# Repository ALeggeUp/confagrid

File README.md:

# Confagrid

What is it?
-----------

Text grid generator tool

Contributors
------------

* [Stephen Legge](https://github.com/slegge)

How to use
----------

* Run `./mvnw package` or `mvnw.cmd package` depending on your platform to compile
* Start the server with `java -jar application/confagrid-webapp/target/confagrid-webapp-0.9.0-SNAPSHOT.jar`
* Open your browser and go to 'http://localhost:8080/'

License
-------

MIT License

Copyright (c) 2017-2018 [ A Legge Up ]

Permission is hereby granted, free of charge, to any person obtaining a copy
of this software and associated documentation files (the "Software"), to deal
in the Software without restriction, including without limitation the rights
to use, copy, modify, merge, publish, distribute, sublicense, and/or sell
copies of the Software, and to permit persons to whom the Software is
furnished to do so, subject to the following conditions:

The above copyright notice and this permission notice shall be included in all
copies or substantial portions of the Software.

Disclaimer
----------

THE SOFTWARE IS PROVIDED "AS IS", WITHOUT WARRANTY OF ANY KIND, EXPRESS OR
IMPLIED, INCLUDING BUT NOT LIMITED TO THE WARRANTIES OF MERCHANTABILITY,
FITNESS FOR A PARTICULAR PURPOSE AND NONINFRINGEMENT. IN NO EVENT SHALL THE
AUTHORS OR COPYRIGHT HOLDERS BE LIABLE FOR ANY CLAIM, DAMAGES OR OTHER
LIABILITY, WHETHER IN AN ACTION OF CONTRACT, TORT OR OTHERWISE, ARISING FROM,
OUT OF OR IN CONNECTION WITH THE SOFTWARE OR THE USE OR OTHER DEALINGS IN THE
SOFTWARE.

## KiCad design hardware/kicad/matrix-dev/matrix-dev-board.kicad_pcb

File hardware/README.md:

# Confagrid Hardware

This folder and subfolders contain the hardware files for Confagrid, they are licensed seperately from the software portion of the project.

# License

This work is licensed under the Creative Commons Attribution 4.0 International License. To view a copy of this license, visit http://creativecommons.org/licenses/by/4.0/ or send a letter to Creative Commons, PO Box 1866, Mountain View, CA 94042, USA.

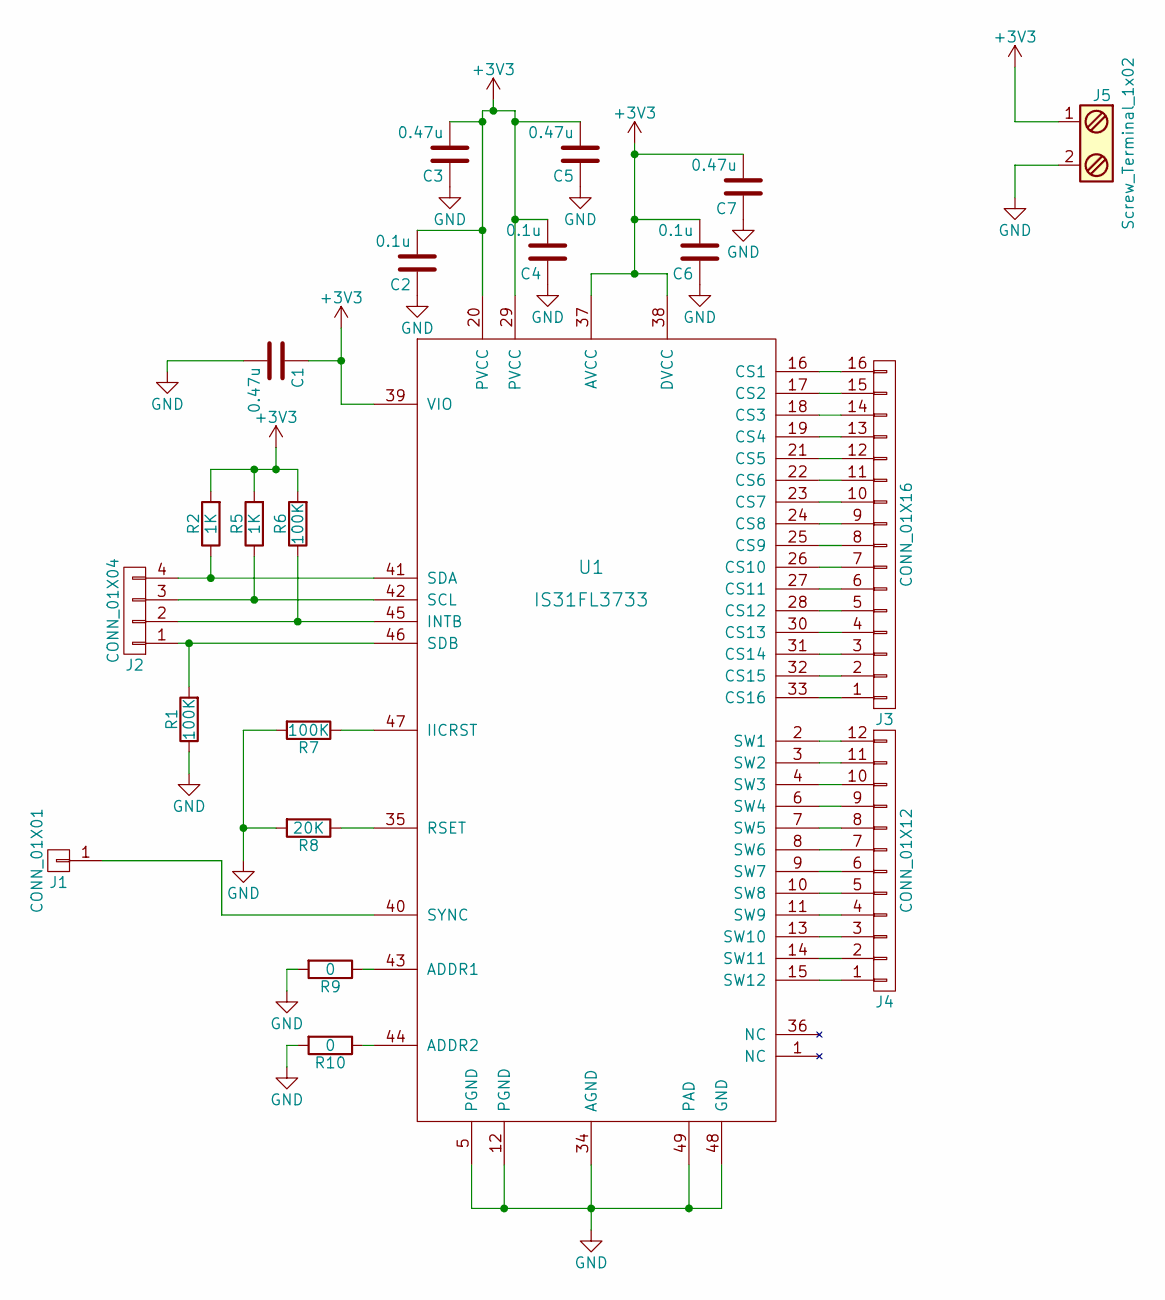
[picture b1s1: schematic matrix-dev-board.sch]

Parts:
C1, C3, C5, C7: 0.47u; C_0805_HandSoldering
C2, C4, C6: 0.1u; C_0805_HandSoldering
J1: CONN_01X01; Pin_Header_Straight_1x01_Pitch1.27mm
J2: CONN_01X04; Pin_Header_Angled_1x04_Pitch1.27mm
J3: CONN_01X16; Pin_Header_Angled_1x16_Pitch1.27mm
J4: CONN_01X12; Pin_Header_Angled_1x12_Pitch1.27mm
J5: Screw_Terminal_1x02; Pin_Header_Straight_1x02_Pitch2.54mm
R1, R6, R7: 100K; R_0805_HandSoldering
R2, R5: 1K; R_0805_HandSoldering
R8: 20K; R_0805_HandSoldering
R9, R10: 0; R_0805_HandSoldering
U1: IS31FL3733; QFN-48-1EP_6x6mm_Pitch0.4mm_ThermalVias

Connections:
+3V3: C1.1, C2.2, C3.2, C4.2, C5.2, C6.2, C7.2, J5.1, R2.2, R5.2, R6.2, U1.20 (PVCC), U1.29 (PVCC), U1.37 (AVCC), U1.38 (DVCC), U1.39 (VIO)
GND: C1.2, C2.1, C3.1, C4.1, C5.1, C6.1, C7.1, J5.2, R1.1, R7.2, R8.2, R9.2, R10.2, U1.5 (PGND), U1.12 (PGND), U1.34 (AGND), U1.48 (GND), U1.49 (PAD)
unnamed: J1.1, U1.40 (SYNC)
unnamed: J2.1, R1.2, U1.46 (SDB)
unnamed: J2.2, R6.1, U1.45 (INTB)
unnamed: J2.3, R5.1, U1.42 (SCL)
unnamed: J2.4, R2.1, U1.41 (SDA)
unnamed: J3.1, U1.33 (CS16)
unnamed: J3.2, U1.32 (CS15)
unnamed: J3.3, U1.31 (CS14)
unnamed: J3.4, U1.30 (CS13)
unnamed: J3.5, U1.28 (CS12)
unnamed: J3.6, U1.27 (CS11)
unnamed: J3.7, U1.26 (CS10)
unnamed: J3.8, U1.25 (CS9)
unnamed: J3.9, U1.24 (CS8)
unnamed: J3.10, U1.23 (CS7)
unnamed: J3.11, U1.22 (CS6)
unnamed: J3.12, U1.21 (CS5)
unnamed: J3.13, U1.19 (CS4)
unnamed: J3.14, U1.18 (CS3)
unnamed: J3.15, U1.17 (CS2)
unnamed: J3.16, U1.16 (CS1)
unnamed: J4.1, U1.15 (SW12)
unnamed: J4.2, U1.14 (SW11)
unnamed: J4.3, U1.13 (SW10)
unnamed: J4.4, U1.11 (SW9)
unnamed: J4.5, U1.10 (SW8)
unnamed: J4.6, U1.9 (SW7)
unnamed: J4.7, U1.8 (SW6)
unnamed: J4.8, U1.7 (SW5)
unnamed: J4.9, U1.6 (SW4)
unnamed: J4.10, U1.4 (SW3)
unnamed: J4.11, U1.3 (SW2)
unnamed: J4.12, U1.2 (SW1)
unnamed: R7.1, U1.47 (IICRST)
unnamed: R8.1, U1.35 (RSET)
unnamed: R9.1, U1.43 (ADDR1)
unnamed: R10.1, U1.44 (ADDR2)

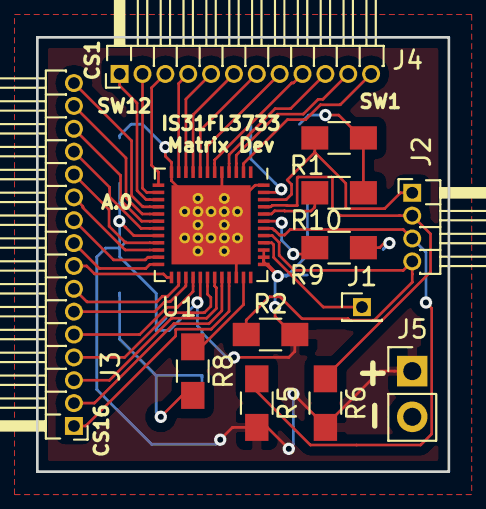
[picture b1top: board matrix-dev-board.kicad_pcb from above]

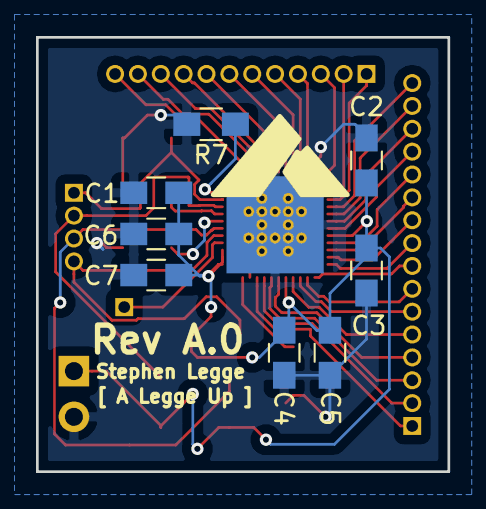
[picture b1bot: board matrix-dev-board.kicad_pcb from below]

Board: 2 copper layers, 22.9 x 24.1 mm, 21 parts (8 on the bottom side), 39 nets.

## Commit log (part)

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2017-07-20 Initial generated files from quickstart archetype with cleanup
2017-07-20 Add the usuals to .gitignore
2017-07-20 Simple class to hold a word
2017-07-20 Class to hold a string of words
2017-07-21 Handle duplicate words in phrases
2017-07-21 DirectedAcyclicWordGraph class to connect all of the word paths
2017-07-21 Add a reverse lookup for the word list
2017-07-21 Initialize DAG with wordlist for verticies and set up adjacent lists
2017-07-21 Change to LinkedHashSet for phrase words because order matters
2017-07-22 Method signature change for clarity
2017-07-23 Change variable names to match getters
2017-07-31 Determine if the digraph has a topological order
2017-08-01 Check several phrases in a test
2017-08-01 Method to retrieve a word from the wordlist by index
2017-08-01 Split out grouping into a new method so that they can be returned
2017-08-01 Add main class to jar in packaging
2017-08-01 Add commons-cli dependency information
2017-08-01 Start command line parser in main class
2017-08-02 Change to option builder style for options
2017-08-02 Make a jar-with-dependencies assembly in the package phase
2017-08-02 Clean up some of the repeated strings with options
2017-08-03 Add toString to wordList so that we can easily dump it
2017-08-03 Method to determine if there are any duplicate words in the phrase
2017-08-04 Keep a list of duplicates in the word list
2017-08-15 Phrases with duplicate words are being tricky
2017-08-15 DupList becomes highest occurrence of each word in the wordlist
2017-08-16 Get the duplicate count of a word in a phrase
2017-08-18 Attempt to sort out multiple occurrences of words in phrases
2017-09-24 Move files into webapp structure with intent to make a webapp
2017-09-25 Copy basic frontend from another project to get started
2017-09-25 Clean up based on TSLint
2017-09-26 Don't need to import component at the app level anymore
2017-09-28 Created a page header with some buttons for navigation
2017-09-28 Remove unused line
2017-09-29 Create a new occurrence of a word to avoid a cycle if/when detected
2017-09-29 Remove reference to deleted debug method
2017-09-30 Add specific version of popper.js for bootstrap dependency
2017-10-01 Change footer into a component
2017-10-01 Add Visual Studio Code directory to ignore list
2017-10-01 Convert header banner into a component
2017-10-01 A new form for creating a new grid
2017-10-01 Remove .less files, not using them
2017-10-02 Clean up inconsistent line endings
2017-10-02 Add configuration for connection to embedded h2 database
2017-10-03 Move RouteController to a common controller package
2017-10-03 Add a 'create' to save to database
2017-10-03 Add some basic details to the README
2017-10-03 Add license to README and update disclaimer to match
2017-10-04 Getter for the id so it is serialized in the response
2017-10-04 Use HttpClient to post to the backend and navigate to edit page
2017-11-27 Set theme jekyll-theme-hacker
2017-12-20 Add zookeeper-cloud dependency
2017-12-20 eslint dependency for vscode support
2017-12-20 Remove zookeeper-discovery dependency for now
2017-12-20 Remove pom import for zookeeper
2017-12-21 Change port to 8080
2017-12-21 Use autocofigured DataSourceProperties
2017-12-21 Update spring-boot version to current
2017-12-28 Add footers to all pages
2017-12-28 Add basic default template
2017-12-28 Add Gemfile to build/run with Jekyll locally
2017-12-28 Add link to open-wink back in
2017-12-28 Fix path to include ALeggeUp organization
2017-12-28 Empty file to create a docs directory for gh-pages
2018-01-03 Simple auth redirect to login form
2018-01-04 Add spring security dependencies
2018-01-04 Correct copyright header
2018-01-04 Simple controller to check role in JWT token
2018-01-06 Reuse common strings in JwtFilter
2018-01-06 Handle case of no roles in claims if not authenticated
2018-01-06 Whitespace cleanup
2018-01-06 Remove auth guard from readonly pages
2018-01-06 Padding above the login form
2018-01-06 Extra padding for some whitespace around the basic login form
2018-01-10 Change to proper authentication service
2018-01-11 Service to get list of existing grids and display titles
2018-01-11 Experimenting with different card layouts
2018-01-11 Consolodate model/entity location and names
2018-01-11 Update imports for moved classes
2018-01-11 Add a configurer to add CORS header for development
2018-01-12 Update login request and response models for type safety
2018-01-14 Initial experiment with apache batik to create svg on demand
2018-01-16 Newer version of Apache Batik with different groupId
2018-01-17 Remove unused packages
2018-01-17 Move version for Apache Batik into dependency management
2018-01-17 Created an application favicon from new logo
2018-01-17 Move models for message exchange into their own package
2018-01-18 Move word grid generation code out into a service to be cleaned up
2018-01-20 Add loop to display posts on main page
2018-01-20 Put excerpt of post into list
2018-01-21 See what the test post looks like with an image
2018-01-21 Fix some config details
2018-01-21 Add current project links and descriptions
2018-01-22 Move inherited posts into draft so that they don't generate pages
2018-01-22 Change to title and subtitle from welcome to be more descriptive
2018-01-22 I think I like 'Pages' instead of 'Log'
2018-01-22 Not sure what impressum is for, I don't think I need it
2018-01-22 Change to custom url
2018-01-23 Change background banner image to something electronics
2018-01-23 Make background of avatar white to make it stand out
2018-01-23 Repositories makes more sense, I think
2018-01-23 Get rid of 'About Me' for now since it's not really about me yet
2018-01-23 Enable disqus comment/forum support
2018-01-23 First post
2018-01-23 Change robots to point to the correct sitemap
2018-01-24 Move old blog content over to github
2018-01-24 Change page title to Labs
2018-01-25 Send back 'authorized' subject in the header or anonymous if unset
2018-01-25 Put anonymous string into a constant
2018-01-25 Remove useless unit test
2018-01-25 Create Mock application for test Spring environments
2018-01-25 Return a mock datasource for unit tests in 'test' profile
2018-01-25 Remove old Main class that isn't used anymore
2018-01-26 :green_heart: Add travis CI instructions
2018-01-27 :memo: [ci skip] Add a code of conduct for the community
2018-01-27 :memo: [ci skip] Add contributing guidelines for the community
2018-01-27 :green_heart: [ci skip] Print log to console as well as to file
2018-01-27 :green_heart: Revert travis config to make sure a failed build is correctly detected
2018-01-27 :memo: [ci skip] Update copyright year to include new year
2018-01-28 :white_check_mark: Add test for JWT Filter
2018-01-28 :white_check_mark: Add silly test for empty exception to get coverage
2018-01-29 :white_check_mark: Add silly tests for config classes to get coverage
2018-01-29 :memo: [ci skip] Add code coverage badge to README documentation
2018-01-30 :white_check_mark: Add test for User Controller
2018-02-01 Exclude model package from jacoco since they don't have anything to test
2018-02-02 :white_check_mark: Add a couple more tests to complete branch coverage on UserController
2018-02-03 :white_check_mark: Add test for WordGridRepository
2018-02-03 :art: Small refactor to clean up controllers
2018-02-04 :white_check_mark: Add simple test for ExperimentalController for coverage
2018-02-05 [ci skip] Refactor into AbstractHttpService to re-use some common code
2018-02-05 [ci skip] Add a simple getRequest to AbstractHttpService and use for WordGrid list
2018-02-05 Remove unused constant
2018-02-06 First implementation of a simple browser storage service
2018-02-09 :white_check_mark: Add simple test in shared module to make sure everything is picked up properly
2018-02-09 Add exclusions to code coverage for bootstrap/config files
2018-02-15 :art: Reformat based on modified checkstyle
2018-02-15 Pass OPTIONS requests through without filtering
2018-02-15 :art: Pull http service out into it's own class
2018-02-15 :memo: Include checkstyle and code format settings as documents
2018-02-17 :white_check_mark: Update JWT filter tests do to change in logic
2018-02-17 Use changed http service
2018-02-17 :white_check_mark: Add tests for check endpoint in User Controller
2018-02-17 Change Mockito.doAnswer parameter to lambda version
2018-02-17 Add date/time service
2018-02-17 :white_check_mark: Add simple tests for DateTimeService
2018-02-18 Convert joda datetime to localdatetime before converting to date
2018-02-18 Correctly mock out expiry date as known value
2018-02-20 :memo: Add a link to the actual docs from the source README
2018-02-20 Fix mapping
2018-02-20 Remove unused import
2018-02-21 :art: Move create request into the word-grid service
2018-02-21 Create a base for requests and responses for consistency
2018-02-22 Add a 'creator' column to word-grid entities
2018-03-02 Set auth token if a different one is returned
2018-03-02 Add anonymous user id and name to response
2018-03-02 Set subject and id in auth responses
2018-03-02 Fix up tests from auth header changes
2018-03-03 Better management of current user
2018-03-03 Only try to parse if something is found in localStorage
2018-03-03 AuthGuard now keyed on current user username
2018-03-03 Rename 'intro' to 'home'
2018-03-03 [ci skip] Add MIT License badge to README
2018-03-03 Determine if a grid is owned by the current user and route accordingly
2018-03-03 Pass edit parameter through to retrieve a word-grid and then start to show
2018-03-07 The only real change is to the sourceSortOrder the rest is reformatting
2018-03-11 Add querydsl dependencies and file reformat
2018-03-11 Add querydsl to wordgrid repository
2018-03-11 Start of phrase and word services
2018-03-11 Add a word grid content endpoint
2018-03-11 Add and models to send wordgrid content between front and backend
2018-03-11 New method in wordgrid service to get grid content
2018-03-11 Add a grid component to the edit view and ability to enter phrases
2018-03-12 Add allowed methods to CORS response to allow PUT
2018-03-12 Switch to a phrase service with a new phrase endpiont
2018-03-12 Use new services to create a new phrase and then add to word-grid
2018-03-12 Update test to handle new allowed methods in system config
2018-03-14 [ci skip] IS31FL3733 component created for Kicad to create a dev board
2018-03-14 [ci skip] Datasheet for the ISSI IS31FL3733
2018-03-14 [ci skip] Add reference to datasheet in the component library
2018-03-15 [ci skip] Fix pull-up and pull-down resistors and add values
2018-03-15 [ci skip] Ignore kicad_pcb backup files
2018-03-15 [ci skip] First attempt at laying out the matrix dev board
2018-03-16 [ci skip] Board 3D render for docs
2018-03-16 [ci skip] Add hardware license info since it is different from the software
2018-03-22 Major refactor of grid calculator
2018-03-22 Edit component can submit phrases and display the existing list
2018-03-22 Add Hackaday logo for link in aside
2018-03-22 Pass string of characters from word grid to frontend
2018-05-11 :art: Refactor into a better structure
2018-05-11 :memo: Add reference to datasheet and digikey page
2018-06-03 Start of firmware part for ESP32
2018-06-03 Add license to header of main
2018-06-03 Create a HardwareConfig skeleton class
2018-06-03 Try to create the animation and start it
2018-06-03 .gitignore to ignore the build artifacts
2018-06-04 New I2C class to wrap i2c initialization
2018-06-05 Re-work task from scratch to fit style
2018-06-05 Toolchain doesn't like block initialization
2018-06-05 Config changes with latest IDF
2018-06-06 Try not resetting before load due to power spike from wifi
2018-06-06 Ignore sdkconfig backup since it's in source control
2018-06-06 Create logger class
2018-06-06 Copy of Digikey cart for matrix dev board
2018-06-06 Reference runTask with nicer looking 'method reference'
2018-06-07 Start simple http server task
2018-06-08 Add simple parsing of http request data to get all the parts
2018-06-10 Auto code cleanup
2018-06-10 Disambiguate the global references to avoid confusion
2018-06-10 Pass I2C class to Animation class
2018-06-10 Initialize I2C and pass to Animation task to get things up and running

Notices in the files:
README.md:
License: CC-BY-SA-4.0
